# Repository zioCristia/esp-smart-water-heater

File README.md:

# Esp smart water heater
Esp8266 based pcb to transform your boiler into a smart one and to integrate it into your autonomous home. 
Any possibility of improvement is accepted.

You can find on Youtube an italian [video tutorial](https://youtu.be/jwHNBpo81dQ) about this project.

## Table of contents
* [General info](#general-info)
* [Hardware](#hardware)
* [Software](#software)
* [Pcb](#pcb)
* [Other usefull things about](#other-usefull-things-about)
  * [Custom software component power on time](#custom-software-component-power-on-time)
  * [Home assistant automations](#home-assistant-automations)

# General info
With this board you can: 
  - control the power on and off of the heater thanks to a relay 
  - measure the temperature of the water 
  - visualize data to an LCD 
  - have a Wi-Fi capability to integrate the heater in your home network 

I've used an esp8266 board powered from an AC-DC transformer. The temperature is measured with a digital thermometer. The LCD is a simple 8x2 display with I2C interface, used to visualize the temperature and the state of the water heater.

The total cost is less than 20€, or 30€ if you also buy the pcb board. The part list link can be found [here](https://docs.google.com/spreadsheets/d/1FqATa8Xt1hETCP2r16k2cSlTp7tTQ170y357NSHGumk/edit?usp=sharing).

# Hardware
The module is composed by:
* esp8266
* 8x2 lcd display with i2c interface
* DS18B20 temperature Sensor
* 20A external relay module
* HLk-5M05 transformer
* 4.7k ohm resistor
* 10k ohm resistor
* 10uF capacitor
* 2N3904 transistor
* external button

The temperature sensor, the relay, the lcd display and the button are external components, connected to the pcb board thanks to 2.54mm pins or directly soldered in the board. The esp is connected thanks to female pins which allow a rapid change of the esp in case of failures. You can think to use jst connectors to avoid orientation problems.

I've used an esp8266 board to reduce the costs. However also the esp32 could be used if made the necessary modifications to the [pcb](#pcb).

The relay I've used is 20A maximum which is sufficient for a 1200W water heater. Please change it in function of your power consumption. 

The transformer allows a more compact design of the pcb without the need to add an external one. You can even think to take the ac L and N from the boiler itself with proper care of short circuits. My connections are made with JST connector and a cable of 22awg.

You can easily change the 8x2 lcd with any other i2c display just by modifying correspondently the code.

# Software
The software I’ve chosen is EspHome so that I could do Over The Air updates and integrate it to my Home Assistant server.

To the default code you just need to add the lines for the control of the relay, the temperature sensor and the display. 

Below you can find the parts to add to the default EspHome code or you can find a complete example of the code [here](/water-heater.yaml.example):

```
# DS18B20 Temperature Sensor
dallas:
  - pin: 
      number: 2
      mode: 
        output: False
        analog: False
        input: True
        open_drain: False
        pullup: False
        pulldown: False
      inverted: False
    
switch:
  - platform: gpio
    name: "Water heater switch"
    pin: GPIO12
    id: rele_boiler
    restore_mode: ALWAYS_OFF

sensor:
  - platform: dallas
    address: 0xd601131bd9e6e328
    name: "Water heater temperature"
    #update_interval: update_time
    id: temperature_sensor
    
i2c:
  sda: GPIO4
  scl: GPIO5
  
display:
  - platform: lcd_pcf8574
    dimensions: 16x2
    id: mydisplay_b
    address: 0x27
    lambda: |-
      static bool bDisplay = true;
      auto now = id(my_time).now(); // local time
      if ((now.hour >= 23 || now.hour < 7) && bDisplay) {
        id(mydisplay_b).no_backlight();;
        bDisplay = false;
      } else if ((now.hour >= 7 && now.hour < 23) && !bDisplay) {
        id(mydisplay_b).backlight();;
        bDisplay = true;
      }
      //it.print("Hello world!");
      it.printf(0,0,"Stat %s", id(rele_boiler).state ? "ON" : "OFF");
      it.printf(0,1,"T %4.1f C", id(sensore_temperatura).state);
      
time:
- platform: sntp
  id: my_time
```

This is the home assistant interface I have created for the water heater:

# Pcb
The pcb design has been made with Eagle and with the intention to have all the components in just one side of the board. For better communications you should add a 3-way JST connector also to the temperature sensor. 

I’ve added the place for an external button in case of some future implementations.

In case you will need some libraries to modify the files, just tell me.

You can find the Eagle's files [here](/smart_water_heater).

# Other usefull things about
## Home assistant automations
To automate the on/off of the boiler I've created some automations which you can find [here](https://github.com/zioCristia/energy-saver-ha-automations#water-heater-automations). They're possible thanks to another [component](https://github.com/zioCristia/esp-energy-monitor) that measure the power consumption of my house as well as the solar power production.

## Custom software component power on time
I've added to my Home Assistant configuration a custom component to monitor the time the water heater has been on. This does not exactly correspond to the time when the water heater consumes 1200W because the heating element turns on and off according to the temperature around it. 
So, especially when we have reached the final temperature, the boiler is on but not active.

Here it is the code:
```
- platform: history_stats
    name: Power on time wh
    entity_id: switch.switch_boiler
    state: "on"
    type: time
    start: "{{ now().replace(hour=0, minute=0, second=0) }}"
    end: "{{ now() }}"
```

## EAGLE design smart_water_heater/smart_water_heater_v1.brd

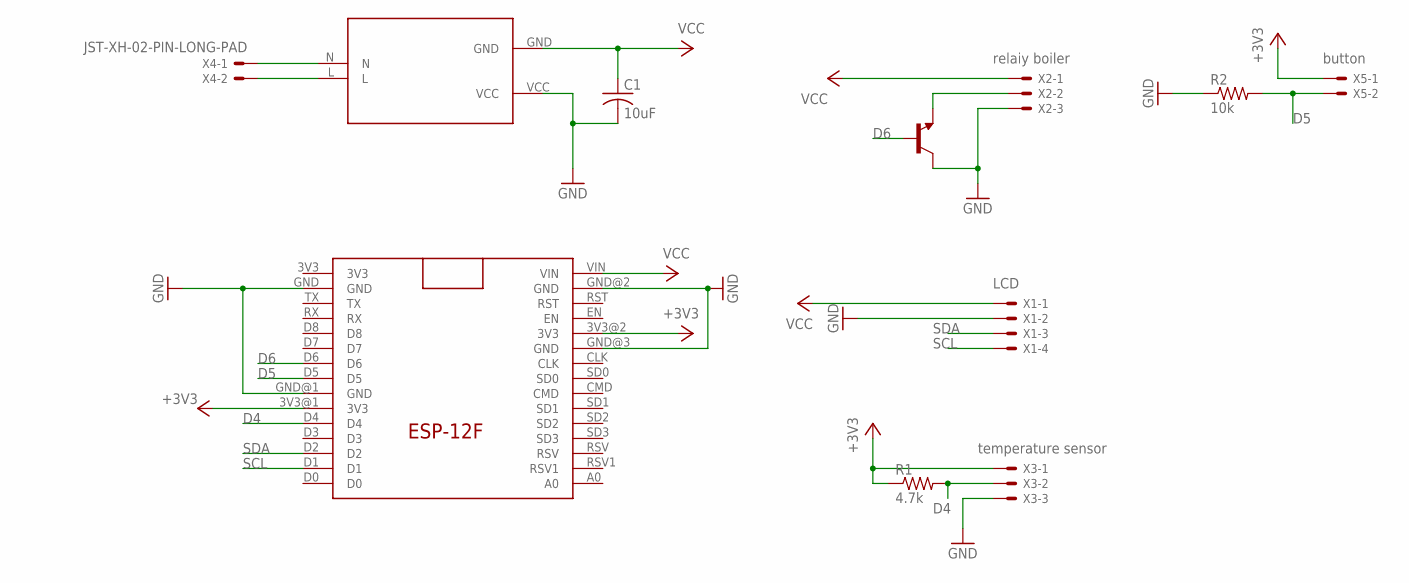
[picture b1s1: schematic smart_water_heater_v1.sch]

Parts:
C1: 10uF; C025-025X050
R1: 4.7k; 0204/7
R2: 10k; 0204/7
T1: 2N2222; TO92-EBC-OVAL
U$1: ESP-12F
U$2: HLK-5M05; CONV_HLK-5M05
X1: 22-23-2041
X2, X3: 22-23-2031
X4: JST-XH-02-PIN-LONG-PAD; JST-XH-02-PACKAGE-LONG-PAD
X5: 22-23-2021

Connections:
+3V3: R1.1, U$1.3V3@1 (3V3), U$1.3V3@2 (3V3), X3.1, X5.1
D4: R1.2, U$1.D4, X3.2
D5: R2.2, U$1.D5, X5.2
D6: T1.B, U$1.D6
GND: C1.2, R2.1, T1.C, U$1.GND, U$1.GND@1 (GND), U$1.GND@2 (GND), U$1.GND@3 (GND), U$2.VCC, X1.2, X2.3, X3.3
unnamed: U$2.N, X4.1
unnamed: U$2.L, X4.2
unnamed: T1.E, X2.2
SCL: U$1.D1, X1.4
SDA: U$1.D2, X1.3
VCC: C1.1, U$1.VIN, U$2.GND, X1.1, X2.1

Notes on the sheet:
relaiy boiler
button
LCD
temperature sensor

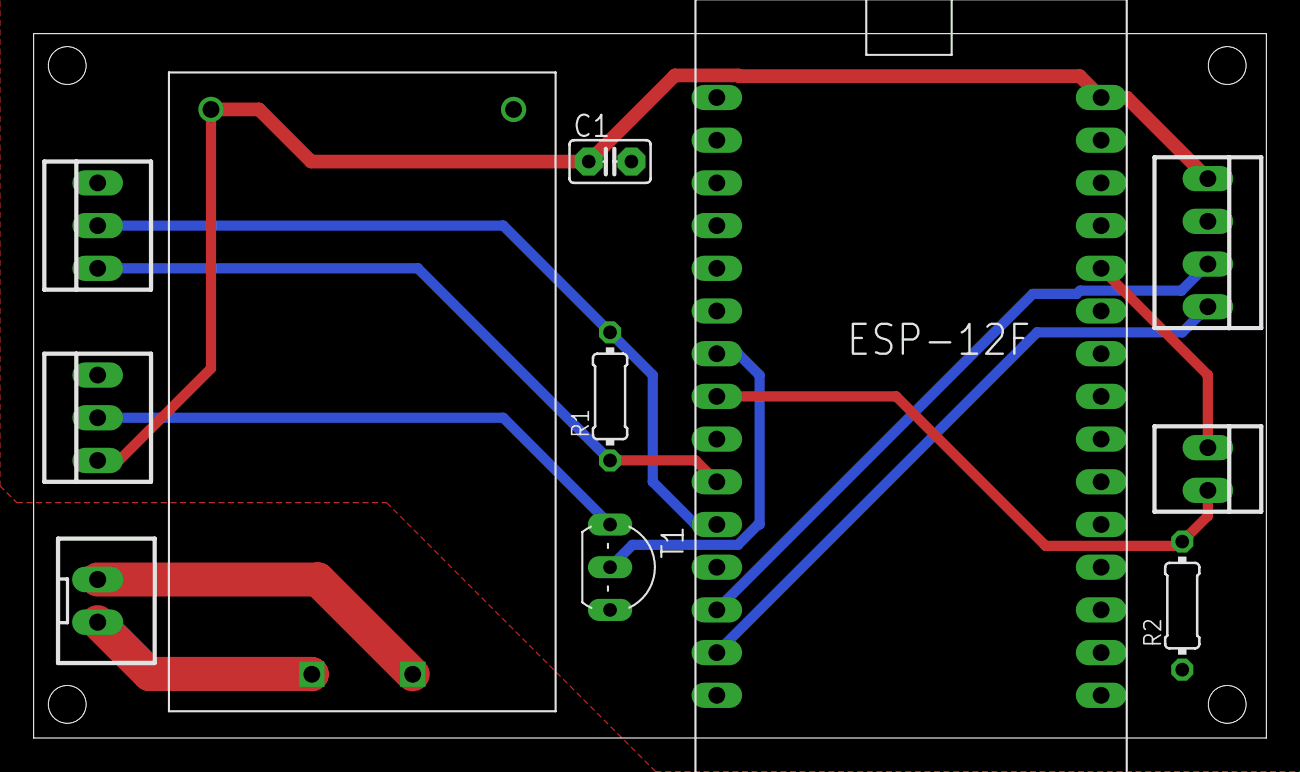
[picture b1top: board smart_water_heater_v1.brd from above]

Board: 2 copper layers, 73.3 x 41.9 mm, 11 parts (0 on the bottom side), 11 nets.

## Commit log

2022-06-03 Rename boiler_slave_v3.brd to smart_water_heater.brd
2022-06-03 Rename boiler_slave_v3.sch to smart_water_heater_v1.sch
2022-06-03 Rename smart_water_heater.brd to smart_water_heater_v1.brd
2022-06-03 Rename boiler_slave_v3.cam to smart_water_heater_v1.cam
2025-03-23 Add CAM outputs
2025-03-24 Add part list link
2025-05-25 Create LICENSE
